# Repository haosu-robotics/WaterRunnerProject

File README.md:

Water Runner Project
====================

Repository for Water Runner Project. Includes Simulink SimMechanics and Python Simulations of open-loop and controlled models of the robot on land and water, circuit board designs, Arduino Code, and various documents.

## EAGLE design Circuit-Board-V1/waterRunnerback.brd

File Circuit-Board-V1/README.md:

Water Runner Board
==================

Known Issues
------------

* Use absolute encoders instead of incremental encoders
    * Absolute encoders output analog signal proportional to the angle and can be read by the Arduino directly via an `AnalogRead()` command.
* Vias near diodes are too close to pads, causing shorts
* Use JST ZE series connectors everywhere instead of JST NSH connectors
    * NSH connectors are too small requiring small wire that breaks easily
    * 28 gauge wire we have for the current ZE connector on the board is  
      thicker than usual and barely fits
* Do not put any circuitry above the Arduino's USB connection as it is grounded
    * A ground plane covering this area is acceptable
* Screw terminal for +7V line is not necessary
    * Use Arduino power supply instead

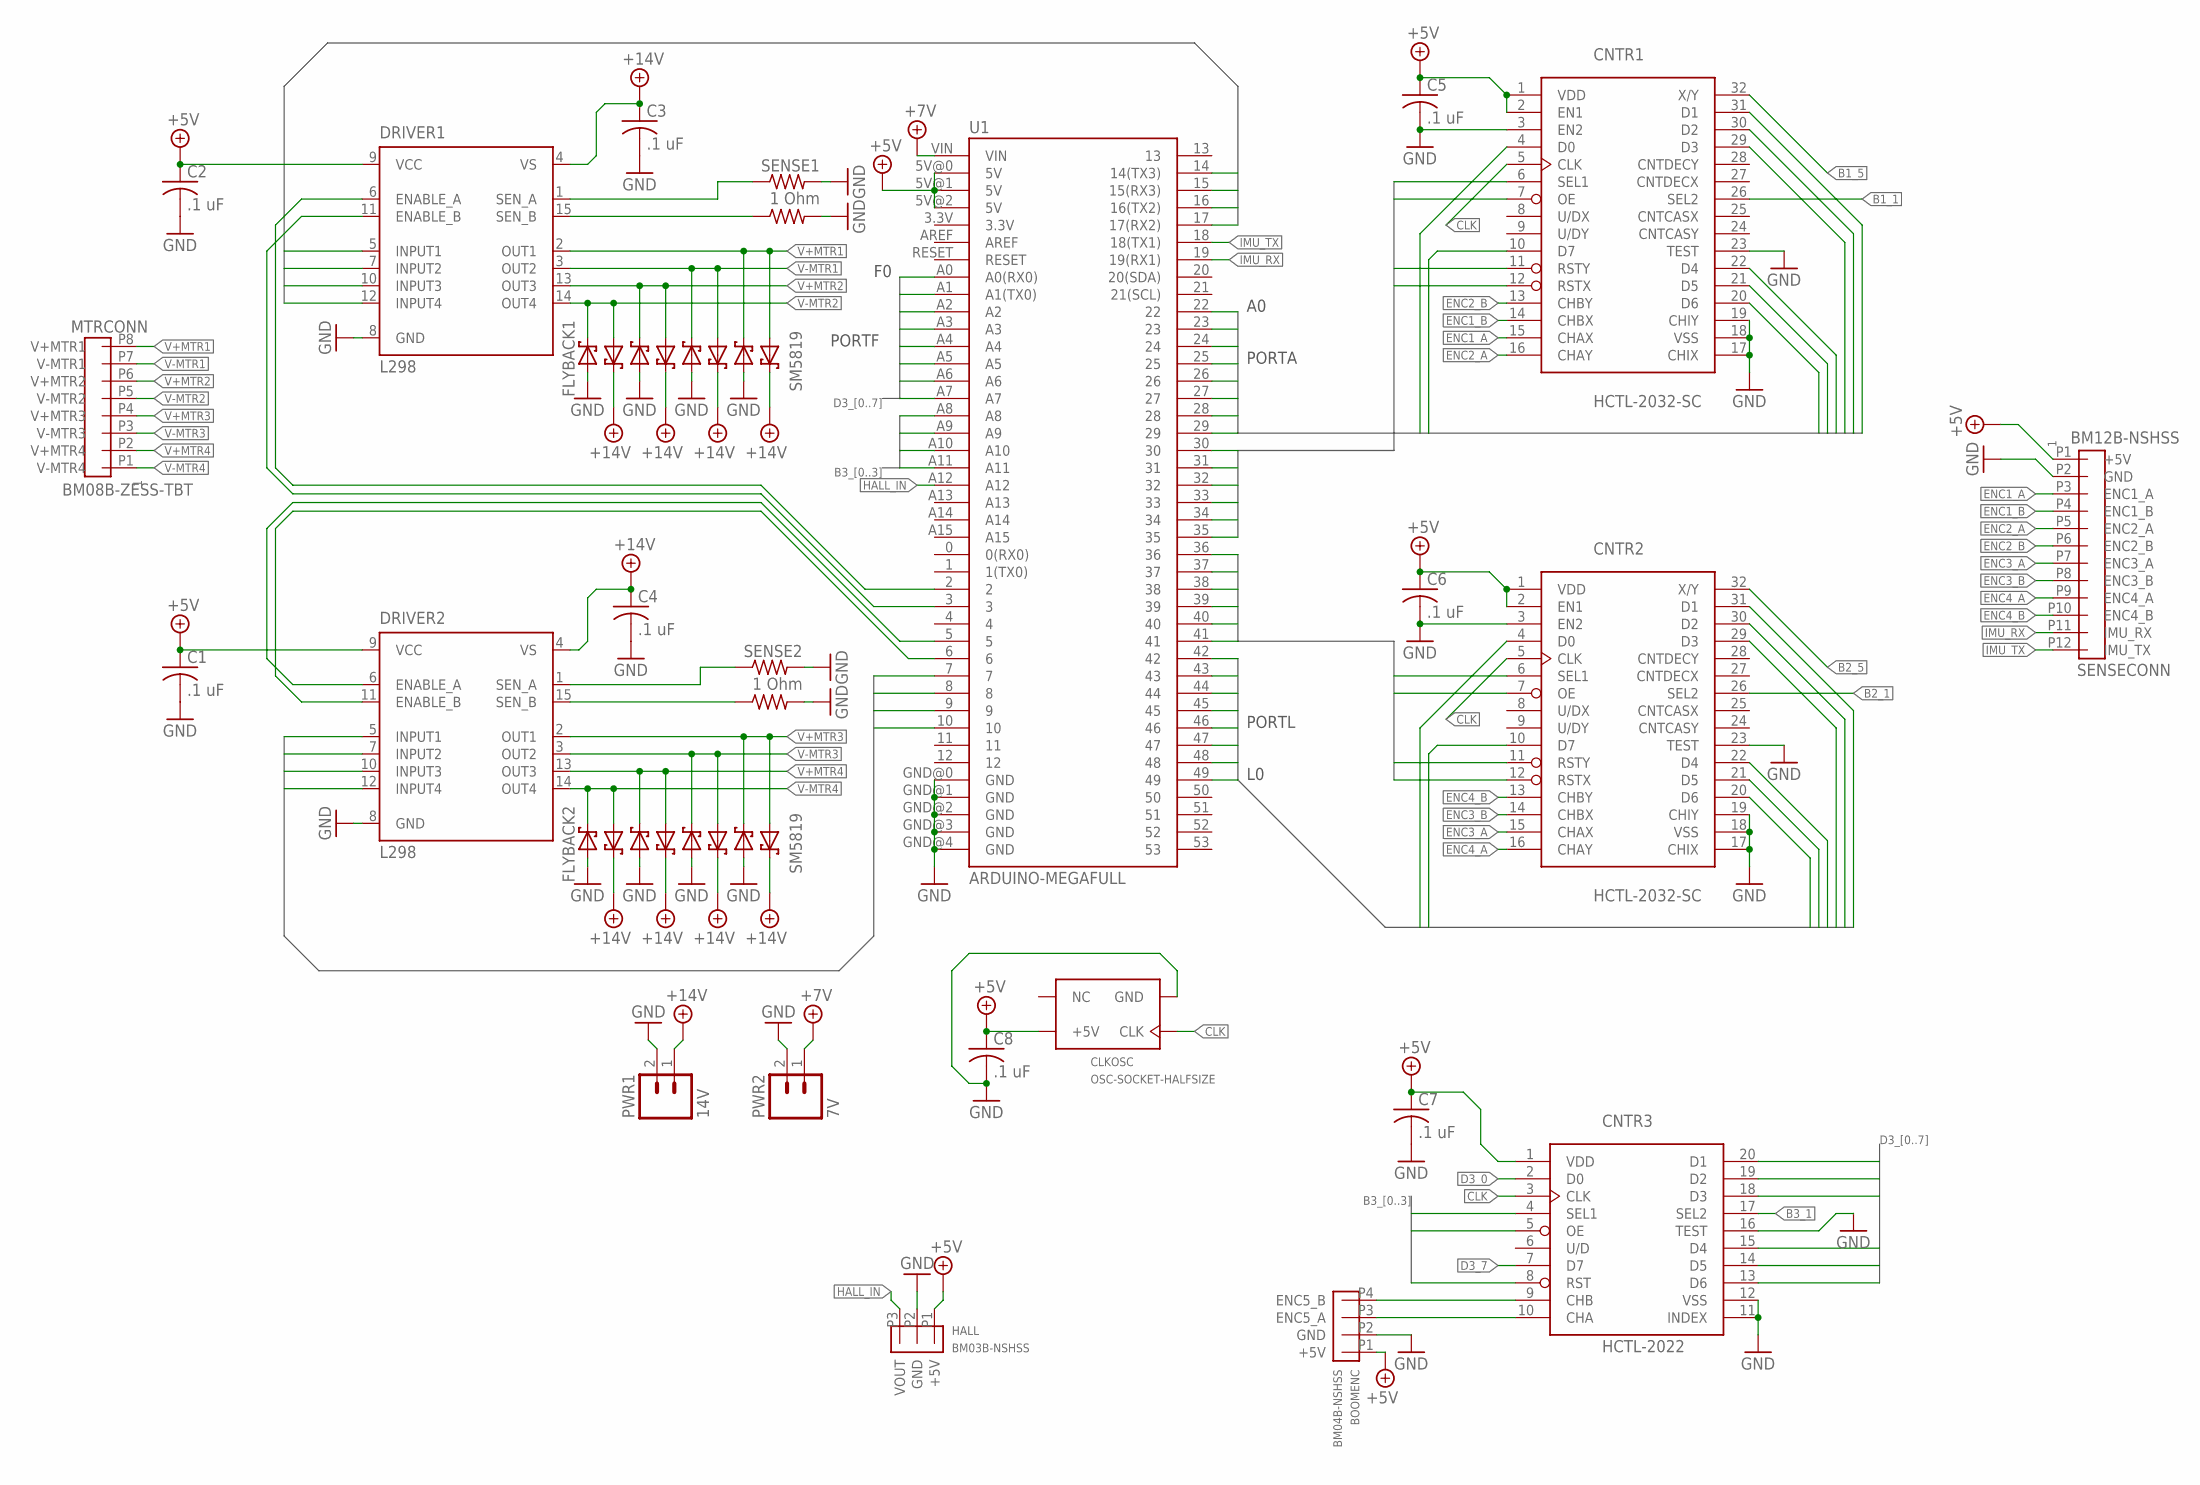
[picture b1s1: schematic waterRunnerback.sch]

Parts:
BOOMENC: BM04B-NSHSS
C1, C2, C3, C4, C5, C6, C7, C8: .1 uF; C1608
CLKOSC: OSC-SOCKET-HALFSIZE
CNTR1, CNTR2: HCTL-2032-SC; SO32W
CNTR3: HCTL-2022; DIL20
DRIVER1, DRIVER2: L298; MULTIWATT-15
FLYBACK1, FLYBACK2: SM5819; SOD123FL
HALL: BM03B-NSHSS
MTRCONN: BM08B-ZESS-TBT
PWR1: 14V; SCREWTERMINAL-5MM-2
PWR2: 7V; SCREWTERMINAL-5MM-2
R1, R2: 1 Ohm; RL1220
SENSE1, SENSE2: 1 Ohm; RL1220
SENSECONN: BM12B-NSHSS
U1: ARDUINO-MEGAFULL; ARDUINO_MEGA
U$1, U$2, U$4, U$5, U$6, U$7, U$9, U$10, U$11, U$12, U$13: SM5817; SOD123FL
U$3, U$8, U$14: SM5819; SOD123FL

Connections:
+5V: BOOMENC.P1 (+5V), C1.1, C2.1, C5.1, C6.1, C7.1, C8.1, CLKOSC.P8 (+5V), CNTR1.1 (VDD), CNTR1.2 (EN1), CNTR2.1 (VDD), CNTR2.2 (EN1), CNTR3.1 (VDD), DRIVER1.9 (VCC), DRIVER2.9 (VCC), HALL.P1 (+5V), SENSECONN.P1 (+5V), U1.5V@0 (5V), U1.5V@1 (5V), U1.5V@2 (5V)
+7V: PWR2.1, U1.VIN
+14V: C3.1, C4.1, DRIVER1.4 (VS), DRIVER2.4 (VS), PWR1.1, U$1.C, U$2.C, U$4.C, U$6.C, U$8.C, U$10.C, U$12.C, U$14.C
B1_0: CNTR1.6 (SEL1), U1.30
B1_1: CNTR1.26 (SEL2), U1.31
B1_2: CNTR1.7 (OE), U1.32
B1_3: CNTR1.11 (RSTY), U1.33
B1_4: CNTR1.12 (RSTX), U1.34
B1_5: CNTR1.32 (X/Y), U1.35
B2_0: CNTR2.6 (SEL1), U1.36
B2_1: CNTR2.26 (SEL2), U1.37
B2_2: CNTR2.7 (OE), U1.38
B2_3: CNTR2.11 (RSTY), U1.39
B2_4: CNTR2.12 (RSTX), U1.40
B2_5: CNTR2.32 (X/Y), U1.41
B3_0: CNTR3.4 (SEL1), U1.A8
B3_1: CNTR3.17 (SEL2), U1.A9
B3_2: CNTR3.5 (OE), U1.A10
B3_3: CNTR3.8 (RST), U1.A11
CLK: CLKOSC.P5 (CLK), CNTR1.5 (CLK), CNTR2.5 (CLK), CNTR3.3 (CLK)
D1_0: CNTR1.4 (D0), U1.22
D1_1: CNTR1.31 (D1), U1.23
D1_2: CNTR1.30 (D2), U1.24
D1_3: CNTR1.29 (D3), U1.25
D1_4: CNTR1.22 (D4), U1.26
D1_5: CNTR1.21 (D5), U1.27
D1_6: CNTR1.20 (D6), U1.28
D1_7: CNTR1.10 (D7), U1.29
D2_0: CNTR2.4 (D0), U1.49
D2_1: CNTR2.31 (D1), U1.48
D2_2: CNTR2.30 (D2), U1.47
D2_3: CNTR2.29 (D3), U1.46
D2_4: CNTR2.22 (D4), U1.45
D2_5: CNTR2.21 (D5), U1.44
D2_6: CNTR2.20 (D6), U1.43
D2_7: CNTR2.10 (D7), U1.42
D3_0: CNTR3.2 (D0), U1.A0 (A0(RX0))
D3_1: CNTR3.20 (D1), U1.A1 (A1(TX0))
D3_2: CNTR3.19 (D2), U1.A2
D3_3: CNTR3.18 (D3), U1.A3
D3_4: CNTR3.15 (D4), U1.A4
D3_5: CNTR3.14 (D5), U1.A5
D3_6: CNTR3.13 (D6), U1.A6
D3_7: CNTR3.7 (D7), U1.A7
ENC1_A: CNTR1.15 (CHAX), SENSECONN.P3 (ENC1_A)
ENC1_B: CNTR1.14 (CHBX), SENSECONN.P4 (ENC1_B)
ENC2_A: CNTR1.16 (CHAY), SENSECONN.P5 (ENC2_A)
ENC2_B: CNTR1.13 (CHBY), SENSECONN.P6 (ENC2_B)
ENC3_A: CNTR2.15 (CHAX), SENSECONN.P7 (ENC3_A)
ENC3_B: CNTR2.14 (CHBX), SENSECONN.P8 (ENC3_B)
ENC4_A: CNTR2.16 (CHAY), SENSECONN.P9 (ENC4_A)
ENC4_B: CNTR2.13 (CHBY), SENSECONN.P10 (ENC4_B)
ENC5_A: BOOMENC.P3 (ENC5_A), CNTR3.10 (CHA)
ENC5_B: BOOMENC.P4 (ENC5_B), CNTR3.9 (CHB)
GND: BOOMENC.P2 (GND), C1.2, C2.2, C3.2, C4.2, C5.2, C6.2, C7.2, C8.2, CLKOSC.P4 (GND), CNTR1.3 (EN2), CNTR1.17 (CHIX), CNTR1.18 (VSS), CNTR1.19 (CHIY), CNTR1.23 (TEST), CNTR2.3 (EN2), CNTR2.17 (CHIX), CNTR2.18 (VSS), CNTR2.19 (CHIY), CNTR2.23 (TEST), CNTR3.11 (INDEX), CNTR3.12 (VSS), CNTR3.16 (TEST), DRIVER1.8 (GND), DRIVER2.8 (GND), FLYBACK1.A, FLYBACK2.A, HALL.P2 (GND), PWR1.2, PWR2.2, R1.P$2 (2), R2.P$2 (2), SENSE1.P$2 (2), SENSE2.P$2 (2), SENSECONN.P2 (GND), U1.GND@0 (GND), U1.GND@1 (GND), U1.GND@2 (GND), U1.GND@3 (GND), U1.GND@4 (GND), U$3.A, U$5.A, U$7.A, U$9.A, U$11.A, U$13.A
HALL_IN: HALL.P3 (VOUT), U1.A12
IMU_RX: SENSECONN.P11 (IMU_RX), U1.19 (19(RX1))
IMU_TX: SENSECONN.P12 (IMU_TX), U1.18 (18(TX1))
IN1_1: DRIVER1.5 (INPUT1), U1.14 (14(TX3))
IN1_2: DRIVER1.7 (INPUT2), U1.15 (15(RX3))
IN1_3: DRIVER1.10 (INPUT3), U1.16 (16(TX2))
IN1_4: DRIVER1.12 (INPUT4), U1.17 (17(RX2))
IN2_1: DRIVER2.5 (INPUT1), U1.7
IN2_2: DRIVER2.7 (INPUT2), U1.8
IN2_3: DRIVER2.10 (INPUT3), U1.9
IN2_4: DRIVER2.12 (INPUT4), U1.10
PWM1: DRIVER1.6 (ENABLE_A), U1.2
PWM2: DRIVER1.11 (ENABLE_B), U1.3
PWM3: DRIVER2.6 (ENABLE_A), U1.5
PWM4: DRIVER2.11 (ENABLE_B), U1.6
SENSE1: DRIVER1.1 (SEN_A), SENSE1.P$1 (1)
SENSE2: DRIVER1.15 (SEN_B), R2.P$1 (1)
SENSE3: DRIVER2.1 (SEN_A), SENSE2.P$1 (1)
SENSE4: DRIVER2.15 (SEN_B), R1.P$1 (1)
V+MTR1: DRIVER1.2 (OUT1), MTRCONN.P8 (V+MTR1), U$13.C, U$14.A
V+MTR2: DRIVER1.13 (OUT3), MTRCONN.P6 (V+MTR2), U$9.C, U$10.A
V+MTR3: DRIVER2.2 (OUT1), MTRCONN.P4 (V+MTR3), U$7.C, U$8.A
V+MTR4: DRIVER2.13 (OUT3), MTRCONN.P2 (V+MTR4), U$3.C, U$4.A
V-MTR1: DRIVER1.3 (OUT2), MTRCONN.P7 (V-MTR1), U$11.C, U$12.A
V-MTR2: DRIVER1.14 (OUT4), FLYBACK1.C, MTRCONN.P5 (V-MTR2), U$1.A
V-MTR3: DRIVER2.3 (OUT2), MTRCONN.P3 (V-MTR3), U$5.C, U$6.A
V-MTR4: DRIVER2.14 (OUT4), FLYBACK2.C, MTRCONN.P1 (V-MTR4), U$2.A

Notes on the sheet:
PORTA
PORTL
PORTF

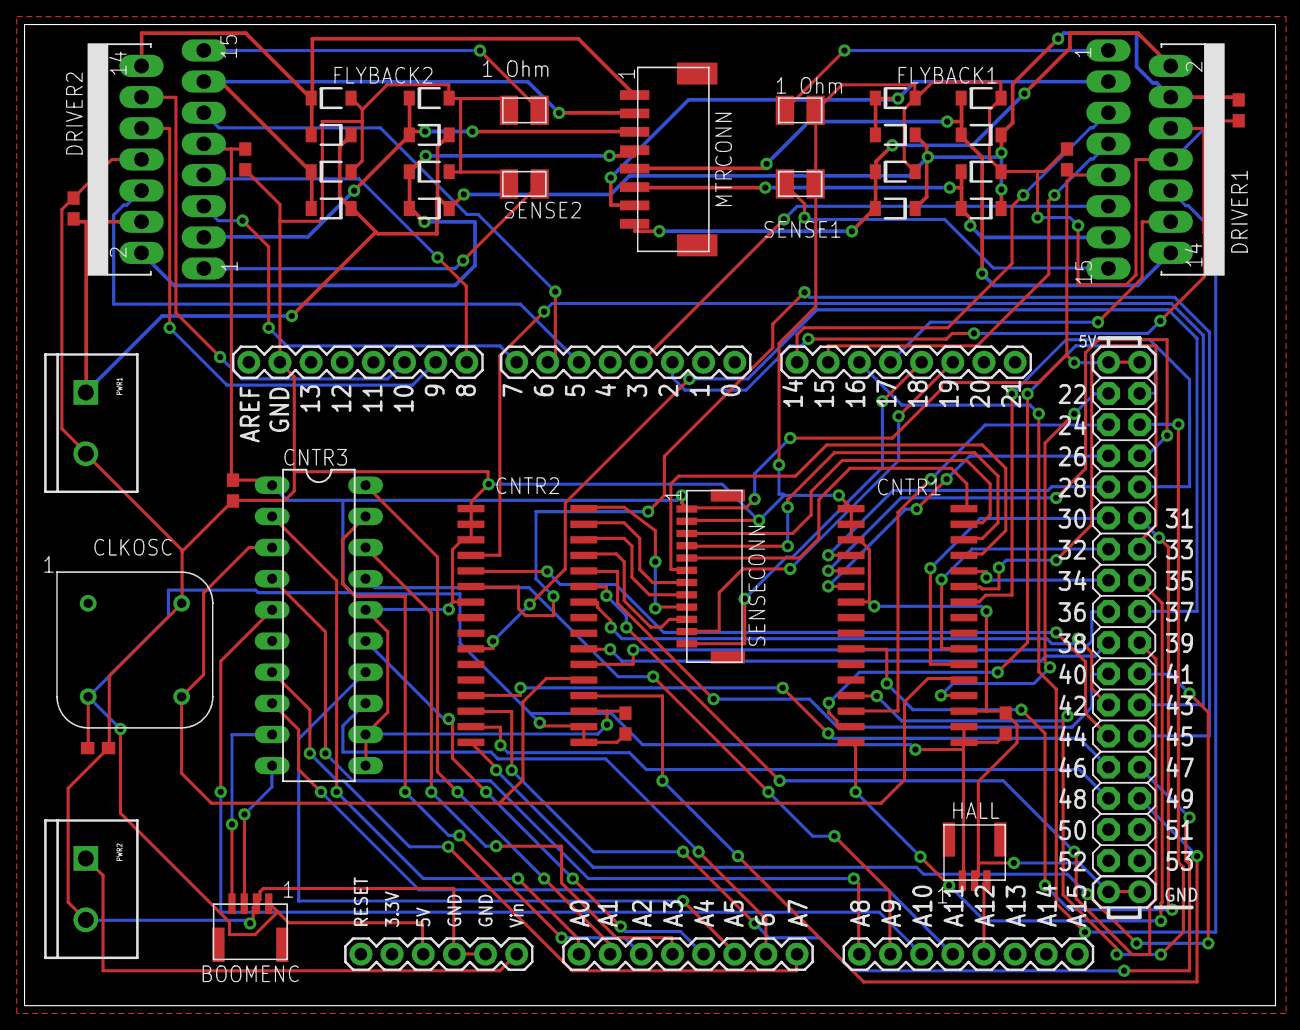
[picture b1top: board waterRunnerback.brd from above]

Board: 2 copper layers, 102.0 x 80.0 mm, 41 parts (0 on the bottom side), 82 nets.

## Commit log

2012-10-13 wrote leg class
2012-10-13 Finished leg position and angle kinematics
2012-10-17 Leg Kinematics working
2012-10-18 Foot speed added
2012-10-18 Added calcForceTorque method in leg class.
2012-10-19 Torque calculation working
2012-10-24 Rewrote with dependency injection
2012-10-25 Fixed foot x-speed calc
2012-10-31 Added hard ground model
2012-11-01 Hard ground implemented
2012-11-01 Finished hard ground
2012-11-05 Implemented PRBM foot but need to add dampening
2012-11-05 Added adams bashforth but its not working yet
2012-11-06 Fixed some issues. Still need to add dampening
2012-11-06 fixed foot bending moment
2012-11-08 Water Running working
2012-11-08 Added x-drag from folded foot
2012-11-20 Have working simulation on water. Started writing report about calculations
2012-11-23 Finished leg kinematics writup
2012-11-27 Wrote footground with its own integrator
2012-11-30 ground running still doesnt work
2012-11-30 Finished writeup of angularly constrained model
2012-12-01 Numerically stable running with constant force ground
2012-12-01 Hard ground working with ab
2012-12-04 Adaptive timestep working. Motor model needs to be fixed.
2012-12-09 Two legged water running working. Started simulink version
2012-12-10 Implmented RK4 for foot integration.
    Added equations for unconstrained pitch to report.
2012-12-10 Added formuas for unconstrained pitch. Need to fix moment equation for robot
2012-12-12 version for math project
2012-12-13 added .gitignore file
2012-12-14 Final report for math
2012-12-19 Water runner made with library files
2013-01-10 Version from first joint presentation
2013-01-16 Tail is working
2013-01-21 Implemented duty factor and got plots for effect of constant duty factor
2013-01-21 Added PRBM foot but there are issues with coordinate systems at foot attach pt
2013-01-21 fix rubber feet
2013-01-22 fix flipping problem
2013-01-25 Using Geyer's 2D ground contact model
2013-01-28 Have DC motor model with PID speed control
2013-01-29 Implemented Bending Rubber Foot Switched to discrete time PID and tuned gains for no load case
2013-01-29 Changed tail and footpad to V2
2013-01-30 adding Body/leg/GroundContact for 2G
2013-02-01 version with tuned motor
2013-02-01 dummy push after creating motor test video
2013-02-05 Gantt chart added
2013-02-06 Schedule v1.0012.13
2013-02-06 New motor block and pattern generator added
2013-02-06 New leg block added
2013-02-06 Started porting water model
2013-02-08 Adding schedule
2013-02-12 after first search
2013-02-13 Bipedal case
2013-02-13 adding matlab figures
2013-02-14 adding result for duty factor
2013-02-18 added numerical and analytic steady-state height and power calculations
2013-02-18 Pushing figures
2013-02-18 Added simulation repos as submodules
2013-02-18 Removed Presentations folder
2013-02-18 Pushing from desktop
2013-02-18 Added submodules to desktop
2013-02-18 Pushing model used for Early Feb presentation
2013-02-18 Adding Water surface runner
2013-02-18 Adding height search simParams
2013-02-18 Updated all submodules
2013-02-18 Updated Gantt Chart
2013-02-23 variable duty factor, first test
2013-02-23 variable duty factor, using PID
2013-02-24 Switchted to Matlab 2012b. Last commit before adding duty factor to SSheight
2013-02-25 changed SSheight functions to include duty factor
2013-02-25 Added duty factor to analytic equation. Comapred to numerical simulation of simple model. Good result
2013-02-25 Perfomed Duty factor and frequency sweek to obtain data to fit simple model to.
2013-02-25 Added Duty Factor to analytical equation for height
2013-02-26 Updated schedule
2013-02-26 Updated schedule. Pulled Most recent Hopper
2013-02-26 nonlinear contorl
2013-02-27 controller for biped
2013-02-27 Fixed Typo in folder name
2013-02-27 Fixed problem with taylor series expansion about DF0
2013-02-27 nonlinear controller fixed
2013-02-28 Started IROS paper
2013-02-28 Commiting one leg stuff before merge
2013-02-28 Updated with first figure
2013-02-28 Split document sections into seperate files
2013-03-01 Added F_avg equation
2013-03-01 Added fit height figure
2013-03-02 Started dynamic walking abstract
2013-03-02 Finished draft of motivation, state of art, and own approach sections
2013-03-02 Edited fit height figure
2013-03-02 Better motivation
2013-03-02 Added figures, moved approach to own tex file, fixed typos
2013-03-02 DW13 added some text
2013-03-02 Changed heading and title size
2013-03-04 Submitted version of dynamic walking abstract
2013-03-04 Submitted Dynamic Walking Abstract
2013-03-04 varibale dutyFactor, adding fourLeg case
2013-03-04 adding fourlegs variable DF
2013-03-05 fixing nonlinear controller
2013-03-06 Draft of KDC proposal
2013-03-06 Created new force equation that is a function of omega_down and omega_up. These equations can be found in OneLeg/SSheight12.m and OneLeg/hfunc12.m. Moved 4leg Variable duty factor model to four leg f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
2013-03-07 Implemented Inverse Dynamic Controller for one legged hopper
2013-03-07 Forced_CPG added
2013-03-11 adding CPF network for four legged system
2013-03-12 CPG schematic is added uner Iros folder
2013-03-13 CPG equations
2013-03-13 adding cpg fig
2013-03-13 CPG math, adding spliting
2013-03-14 Started 3 DOF inverse dynamics controller
2013-03-14 Started 3DOF closed loop CPG controller
2013-03-15 Coupled controller is working in roll and height directions
2013-03-15 Proof read Mahdi's part of the document
2013-03-15 Added section about inverse dynamics controller
2013-03-17 Tuned Gains. Added simulated waves
2013-03-18 Added scope for omegas produced by CPG. Reduced D gains
2013-03-18 Fixed error in moment arm vectors and matrices
2013-03-20 Water model simplification, first commit
2013-03-21 Added meeting notes
2013-03-25 new water contact model, no integratioin
2013-03-30 Step response and simulated wave response complete.
2013-04-16 Calibrated hopper with heavier weight
2013-04-16 updated hopper model with new weight added arduino repo with hello world added website
2013-04-16 added extra folders to .gitignore
2013-04-26 Full robot simulation with new water contact
2013-04-27 Fixed sinking Problem. Tail does not work.
2013-04-27 minor fixes for water contacts in Tail and legs
2013-04-27 Major fix for water drag force, using local coordinate was wrong
2013-04-28 Have good response to input torque wave with anti windup feedback
2013-04-29 Disturbance torque results
2013-04-29 Calibrated hopper model for V2 water runner
2013-04-29 Implemented Controller on V2 sim
2013-04-30 Version for KDC project presentation results
2013-05-01 Started modeling simple linear system
2013-05-02 Started adding roll pitch dynamics
2013-05-02 Added roll, pitch dynamics, but there is an instability
2013-05-02 Have lienarized controller working
2013-05-02 Nonlinear state dynamics version
2013-05-03 Created 2d linear controller for full robot sim
2013-05-12 PID motor control working
2013-05-12 Made plots for KDC final project report
2013-05-12 Added closed loop model to V1 sim. Too slow.
2013-05-12 Produced plots for KDC final report
2013-05-12 Up to date simulations and Robot Code
2013-05-12 removed extra simParam
2013-05-12 fixed extra simparam issue
2013-05-12 Fixed issues with extra simParam files
2013-05-13 Almost done with KDC project paper
2013-05-13 Finished rough draft of KDC final project report
2013-05-14 Finished second draft
2013-06-03 Started Dynamic Walking poster
2013-06-03 Got result with heuristic to push to trot gait
2013-06-03 added pdfs
2013-06-04 First draft of poster done
2013-06-04 cleanup
2013-06-06 Near final version
2013-06-17 Fit params added
2013-06-17 Got rid of redundant files
2013-06-24 Updated KDC project
2013-06-24 Final poster
2013-06-24 Dynamic Walking Poster
2013-06-24 Fixed switched leg speed inputs into CPG :
2013-06-24 updated sim
2013-06-24 All sims up to date
2013-06-24 Started proposal
2013-08-07 Moved Documents to Research Folder
2013-08-07 Added Readme Files
2013-08-07 Added Readme Files. Reorganized
2013-08-07 Updated Water Runner Code Files
2013-08-07 Synced images between office computer and desktop
2013-08-07 Added V1 Circuit Board
2013-08-07 Uploading document pdfs
2013-08-07 Added more README files
2013-08-07 Updated main README file
2013-08-08 Added code for simulink-arduino control.

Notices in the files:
parts and their libraries:
SparkFun-Boards: Licensing: CC v3.0 Share-Alike You are welcome to use this library for commercial purposes.
